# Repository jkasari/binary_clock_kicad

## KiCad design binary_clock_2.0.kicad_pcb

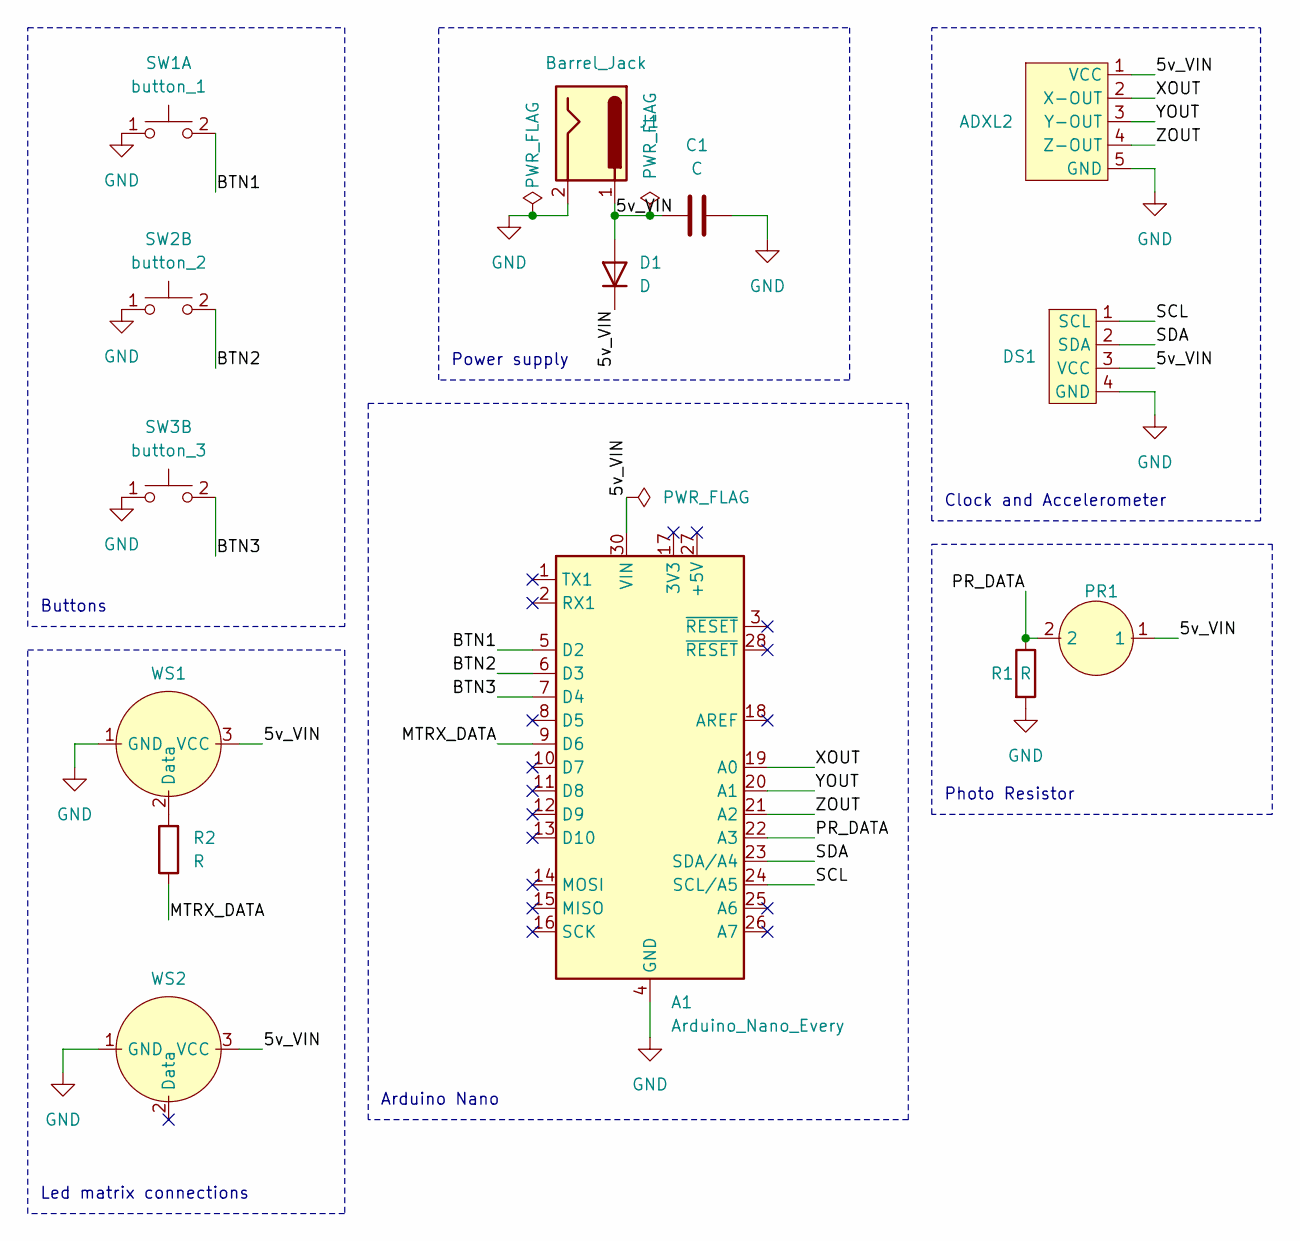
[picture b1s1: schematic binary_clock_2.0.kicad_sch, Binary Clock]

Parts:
A1: Arduino_Nano_Every; Arduino_Nano
ADXL2: ADXL3335
C1: C; CP_Radial_D10.0mm_P5.00mm
D1: D; D_DO-15_P12.70mm_Horizontal
DS1: D3231
J1: Barrel_Jack; BarrelJack_Horizontal
PR1: double_solder_pad
R1, R2: R; R_Axial_DIN0309_L9.0mm_D3.2mm_P12.70mm_Horizontal
SW1: button_1; double_solder_pad
SW2: button_2; double_solder_pad
SW3: button_3; double_solder_pad
WS1, WS2: WS2812_matrix

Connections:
/5v_VIN: A1.30 (VIN), ADXL2.1 (VCC), C1.1, D1.1 (K), D1.2 (A), DS1.3 (VCC), J1.1, PR1.1, WS1.3 (VCC), WS2.3 (VCC)
/BTN1: A1.5 (D2), SW1.2 (D)
/BTN2: A1.6 (D3), SW2.2
/BTN3: A1.7 (D4), SW3.2
/MTRX_DATA: A1.9 (D6), R2.1
/PR_DATA: A1.22 (A3), PR1.2, R1.1
/SCL: A1.24 (SCL/A5), DS1.1 (SCL)
/SDA: A1.23 (SDA/A4), DS1.2 (SDA)
/XOUT: A1.19 (A0), ADXL2.2 (X-OUT)
/YOUT: A1.20 (A1), ADXL2.3 (Y-OUT)
/ZOUT: A1.21 (A2), ADXL2.4 (Z-OUT)
GND: A1.4 (GND), A1.29 (GND), ADXL2.5 (GND), C1.2, DS1.4 (GND), J1.2, R1.2, SW1.1 (C), SW2.1, SW3.1, WS1.1 (GND), WS2.1 (GND)
unnamed: R2.2, WS1.2 (Data)

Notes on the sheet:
Clock and Accelerometer
Led matrix connections
Buttons
Photo Resistor
Arduino Nano
Power supply

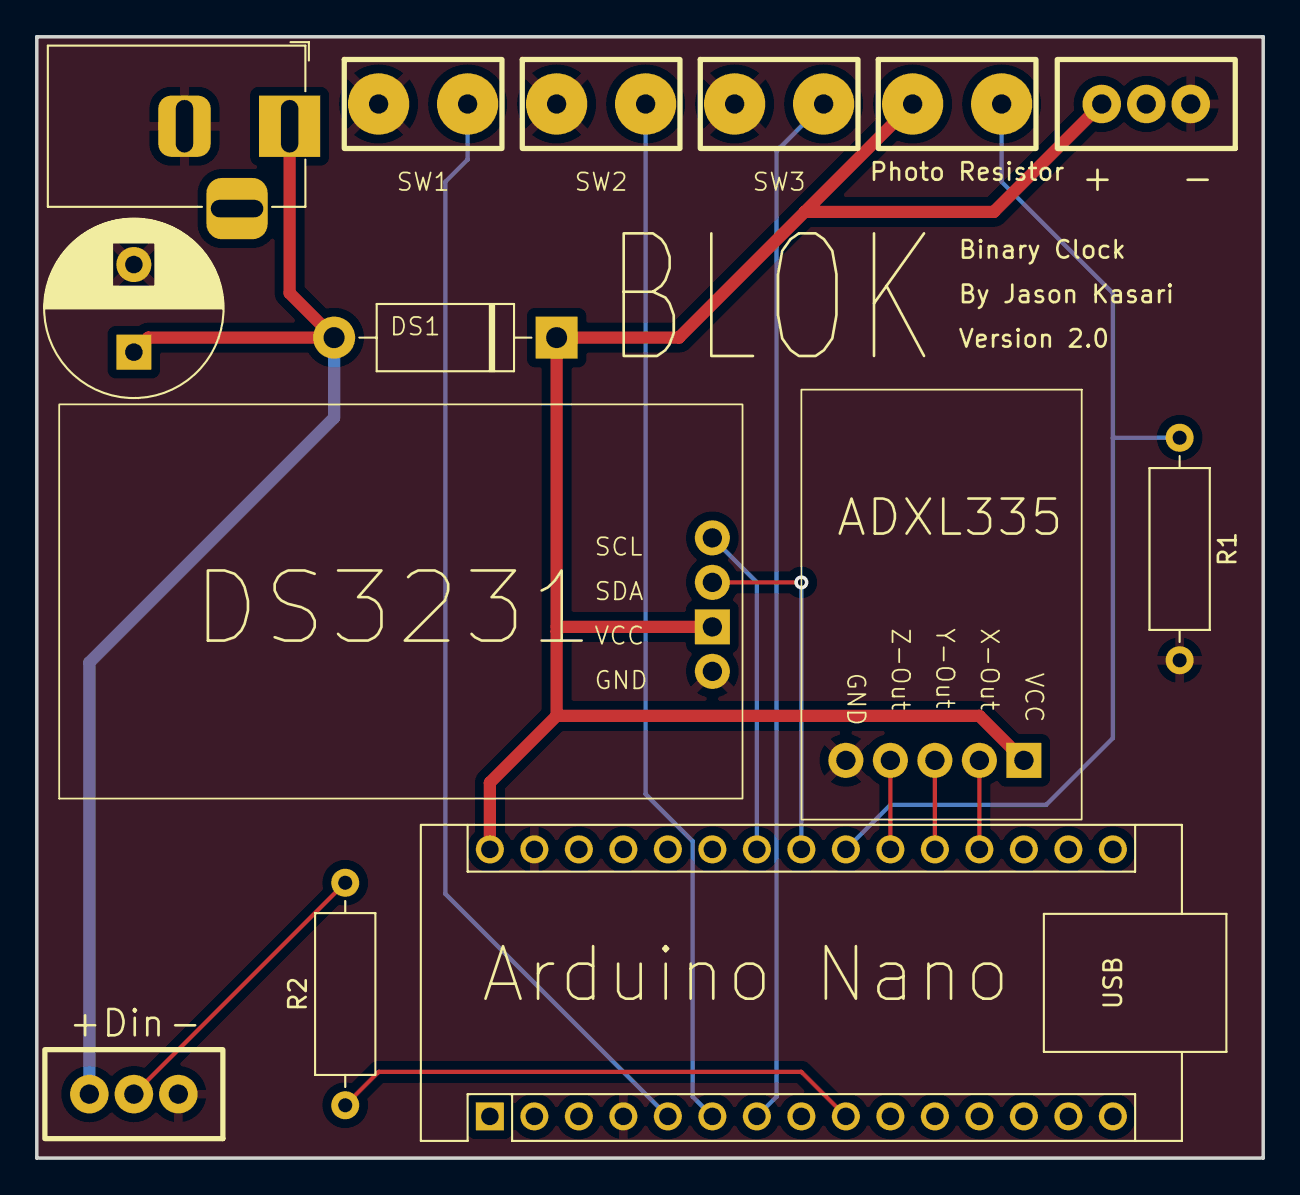
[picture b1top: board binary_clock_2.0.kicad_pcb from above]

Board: 2 copper layers, 70.0 x 64.0 mm, 14 parts (0 on the bottom side), 13 nets.

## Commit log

2024-01-14 First init
